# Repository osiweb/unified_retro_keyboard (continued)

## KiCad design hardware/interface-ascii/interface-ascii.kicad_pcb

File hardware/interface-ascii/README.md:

# ASCII Interface - Atmega328p

This is is a key scanner module with parallel output, and optional serial
output, supporting keyboards of up to 16 rows X 8 columns.

The ATMega 328P was selected for the sole reason that it is an architecture
familiar to many hobbyists, with an accessible programming environment and
ecosystem, in a DIP format that fits the retro look and is easy to solder for
most hobbyists. All of the ICs, other than the microcontroller, are only present
to compensate for the limited number of GPIO lines on this small 28-pin
microcontroller. Using a bigger chip would greatly simplify the hardware and
even slightly simplify the hardware layer of the firmware.

## Features
- Parallel or serial output
- Up to 8 configuration settings via an up-to-8 position DIP switch
- Apple 1, Apple 2, and SOL-20 compatible outputs. Other configurations can be
  supported by making a custom cable.
- Can decode arbitrary keyboards up 16 rows by 8 columns.
- Supports up to 3 keyboard LEDs
- Supports up to 3 "special" host outputs, such as RESET, SCREEN_CLEAR, BREAK, etc.

## Overview
- The keyboard rows are driven by a pair of 74LS138 decoders, allowing 4 GPIO
  lines to drive 16 rows.
- The columns are read in via an 8-bit shift register, controlled by 3 GPIO lines.
- One 8-bit port is used for the parallel ASCII output.
- Three GPIO lines are used to generate special outputs to the host. These could
  be RESET, BREAK, CLEAR, etc. Two of these may be configured as emulated
  open-collector drivers.
- Three GPIO lines are used to control keyboard LEDs. 

- The DIP switch is wired into row 8 (of 0-15) to reduce RAM usage and speed up
  key scanning.

- The top two parallel I/O bits can also be configured as UART I/O. This could
be used to provide serial output instead or parallel output, to support a
bootloader, or even to accept a serial input stream from another computer to
send to the host as parallel ASCII data. This last application would require
careful timing to avoid conflicts.

## Assembly Notes

The minimum functioning circuit includes 
1. the Microcontroller (U1)
1. the 74LS166 shift register (U2)
1. one 74LS138 decoder (U3). This means no DIP switch, so keymap must be
   selected at firmware build.
1. The resistor network RN1
1. The two resistors R3 and R4. If you are using the keyboard in only a parallel
configuration or only a serial configuration, then you can jumper these
resistors with a piece of wire.
1. Any connectors required.

## Optional components
### Diodes D1-D16
These diodes are intended to prevent conflicts between high and low keyboard
driver outputs. They allow the row drivers to pull rows low, but not high,
emulating open collector outputs.

If you are attaching a keyboard with no diodes, then you only need to populate
the diodes corresponding to rows on the keyboard. If the keyboard has 8 rows,
then you may want to install 8 diodes corresponding to those rows.

Note that the footprints for these diodes include a copper jumper on the TOP
copper layer. If you install any of these diodes, you should cut the jumpers for
those diodes. Otherwise the diodes do nothing.

If you are attaching a keyboard with a diode per key, then the diodes on the keys perform the same function, in addition to preventing "ghosting", so the per-row diodes do not need to be installed.

### DIP switch and associated diodes
If you don't want to select keymaps or options via the DIP switch, then you may omit the DIP switch and diodes.  If you do this, then you will have to set the keymap and all preferences in the firmware.
DIP switches, you can set all your preferences in the firmware, or just accept
the default behavior, and skip the DIP switch and Diodes D17-D20 and D24-D27.

### Second 74LS138 multiplexer (U4)
Only needed if you have more than 8 rows (including the DIP switch).

### The 74LS07 hex buffer (U5) and pullup R6
The 74LS07 is only needed if you are using LED2 or LED3 on the keyboard, or the OUT2 open
collector output.

### Diodes D21, D22, D23
Some keyboards may not wire all keys into the matrix. For example, some other
interface modules may assign special hardware functions to certain keys. Those
keys are brought directly to the keyboard connector. For the classic keyboard,
the POWER key, the '@' key, and the RUBOUT key are not directly wired. This
module wires them into the matrix via D21, D22, and D23, respectively. For
keyboards with no separately wired keys, these diodes may be omitted.

### Resistors R1, R2, R5
These resistors provide current limiting for up to three keyboard LEDs. If no
keyboard LEDs are installed, then these resistors can be ommitted.

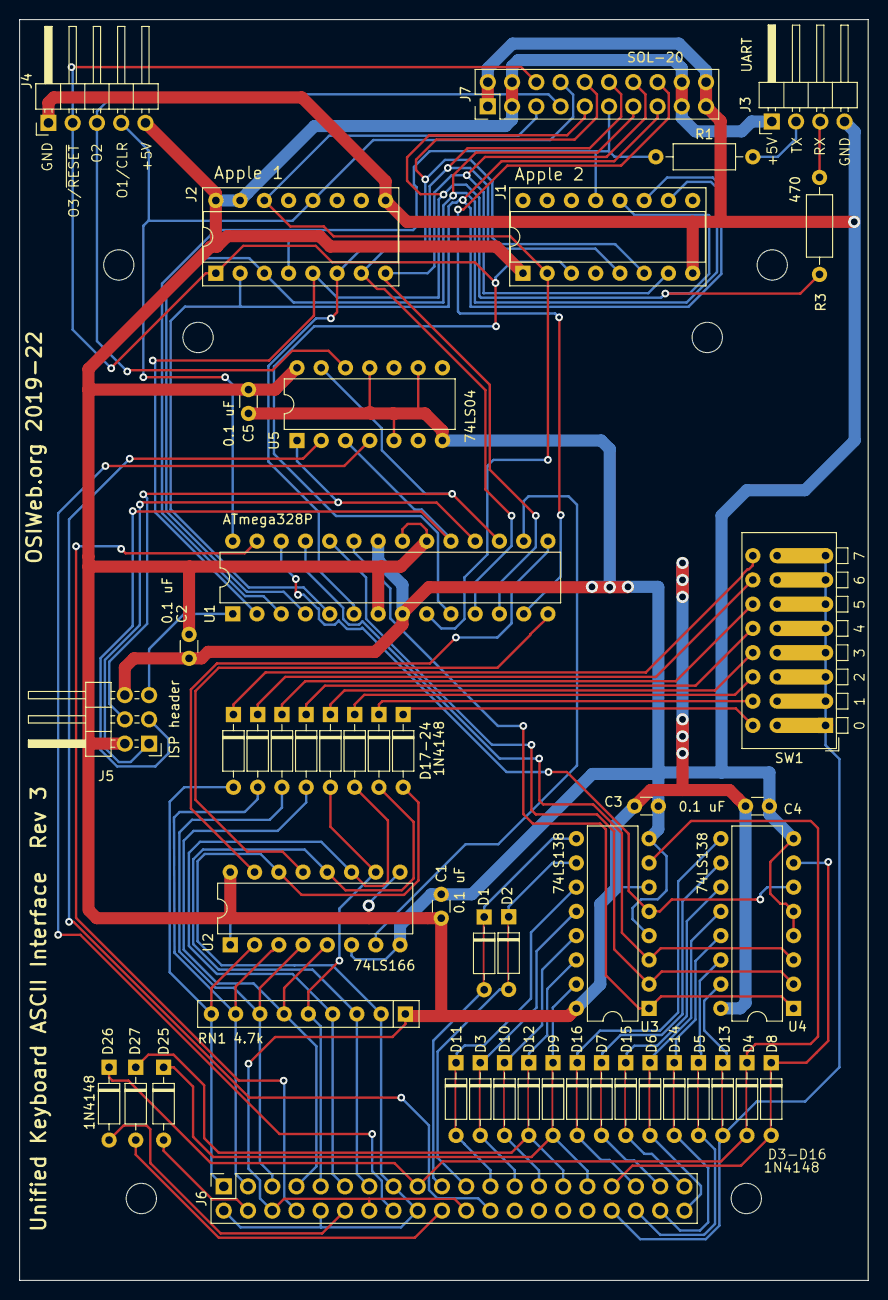
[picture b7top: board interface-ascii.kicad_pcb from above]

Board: 2 copper layers, 88.9 x 132.1 mm, 48 parts (0 on the bottom side), 81 nets.

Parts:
C1, C2, C3, C4, C5: 0.1 uF; C_Disc_D3.0mm_W1.6mm_P2.50mm
D1, D2, D3, D4, D5, D6, D7, D8, D9, D10, D11, D12, D13, D14, D15, D16: 1N4148; D_DO-35_SOD27_P7.62mm_Horizontal_bypassed
D17, D18, D19, D20, D21, D22, D23, D24, D25, D26, D27: 1N4148; D_DO-35_SOD27_P7.62mm_Horizontal
J1: Apple 2; DIP-16_W7.62mm_Socket
J2: Apple 1; DIP-16_W7.62mm_Socket
J3: UART; PinHeader_1x04_P2.54mm_Horizontal
J4: Outputs; PinHeader_1x05_P2.54mm_Horizontal
J5: ISP header; PinHeader_2x03_P2.54mm_Horizontal
J6: Keyboard; kbd_header_and_mounting_holes
J7: SOL-20; SOL20-header-vertical
R1, R3: 470; R_Axial_DIN0207_L6.3mm_D2.5mm_P10.16mm_Horizontal
RN1: 4.7k; R_Array_SIP9
SW1: Options; SW_DIP_SPSTx08_oriented_backward
U1: ATmega328P; DIP-28_W7.62mm
U2: 74LS166; DIP-16_W7.62mm
U3, U4: 74LS138; DIP-16_W7.62mm
U5: 74LS04; DIP-14_W7.62mm

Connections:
+5V: C1.1, C2.1, C3.1, C4.1, C5.1, J1.1, J2.15, J2.16, J3.1, J4.5, J5.2, J6.6, J6.14, J6.22, J7.2, J7.9, J7.12, J7.19, RN1.1 (common), U1.7 (VCC), U1.20 (AVCC), U1.21 (AREF), U2.1 (Ds), U2.9 (Clr), U2.16 (VCC), U3.6 (E3), U3.16 (VCC), U4.16 (VCC), U5.14 (VCC)
/Col0: D17.2 (A), J6.2, J6.10, J6.15, J6.18, RN1.2 (R1), U2.14 (D0)
/Col1: D21.2 (A), J6.13, RN1.3 (R2), U2.12 (D1)
/Col2: D18.2 (A), J6.11, RN1.4 (R3), U2.11 (D2)
/Col3: D22.2 (A), J6.9, RN1.5 (R4), U2.10 (D3)
/Col4: D19.2 (A), J6.7, RN1.6 (R5), U2.5 (D4)
/Col5: D23.2 (A), J6.5, RN1.7 (R6), U2.4 (D5)
/Col6: D20.2 (A), J6.3, RN1.8 (R7), U2.3 (D6)
/Col7: D24.2 (A), J6.1, RN1.9 (R8), U2.2 (D7)
/D0: J1.12, J2.5, J7.5, R3.1, U1.2 (PD0)
/D1: J1.13, J2.4, J7.6, R1.1, U1.3 (PD1)
/D2: J1.10, J2.3, J7.7, U1.4 (PD2)
/D3: J1.11, J2.2, J7.8, U1.5 (PD3)
/D4: J1.6, J2.6, J7.15, U1.6 (PD4)
/D5: J1.5, J2.7, J7.16, U1.11 (PD5)
/D6: J1.7, J2.8, J7.17, U1.12 (PD6)
/D7: J7.18, U1.13 (PD7)
/LED1: J6.8, U1.27 (PC4)
/MISO-LED3: J5.1, U1.18 (MISO/PB4), U5.1
/MOSI-OUT2: J5.4, U1.17 (MOSI), U5.13
/OUT1: J2.12, J4.4, J7.14, U1.28 (PC5)
/OUT2: J4.3, J7.4, U5.12
/OUT3: J1.3, J2.1, J4.2, J7.13, U1.10 (PB7)
/Row0: D9.2 (A), D25.1 (K), J6.31
/Row1: D12.2 (A), D27.1 (K), J6.29
/Row2: D10.2 (A), J6.27
/Row3: D3.2 (A), J6.25
/Row4: D11.2 (A), J6.23
/Row5: D2.2 (A), J6.21
/Row6: D1.2 (A), J6.19
/Row7: D4.2 (A), D26.1 (K), J6.17
/Row8: D13.2 (A), J6.34, SW1.1, SW1.2, SW1.3, SW1.4, SW1.5, SW1.6, SW1.7, SW1.8
/Row9: D5.2 (A), J6.36
/Row10: D14.2 (A), J6.38
/Row11: D6.2 (A), J6.40
/Row12: D15.2 (A), J6.39
/Row13: D7.2 (A), J6.37
/Row14: D16.2 (A), J6.35
/Row15: D8.2 (A), J6.33
/Rx: J3.3, R3.2
/SCK-LED2: J5.3, U1.19 (SCK/PB5), U5.3
/Tx: J3.2, R1.2
/~RESET: J5.5, U1.1 (~RESET)
/~STROBE: J1.2, J2.14, J7.3, U1.9 (PB6)
GND: C1.2, C2.2, C3.2, C4.2, C5.2, J1.8, J2.9, J3.4, J4.1, J5.6, J7.1, J7.10, J7.11, J7.20, U1.8 (GND), U1.22 (GND), U2.6 (CK_INH), U2.8 (GND), U3.4 (E1), U3.8 (GND), U4.4 (E1), U4.5 (E2), U4.8 (GND), U5.5, U5.7 (GND), U5.9, U5.11
unnamed: D1.1 (K), U3.9 (O6)
unnamed: D2.1 (K), U3.10 (O5)
unnamed: D3.1 (K), U3.12 (O3)
unnamed: D4.1 (K), U3.7 (O7)
unnamed: D5.1 (K), U4.14 (O1)
unnamed: D6.1 (K), U4.12 (O3)
unnamed: D7.1 (K), U4.10 (O5)
unnamed: D8.1 (K), U4.7 (O7)
unnamed: D9.1 (K), U3.15 (O0)
unnamed: D10.1 (K), U3.13 (O2)
unnamed: D11.1 (K), U3.11 (O4)
unnamed: D12.1 (K), U3.14 (O1)
unnamed: D13.1 (K), U4.15 (O0)
unnamed: D14.1 (K), U4.13 (O2)
unnamed: D15.1 (K), U4.11 (O4)
unnamed: D16.1 (K), U4.9 (O6)
unnamed: D17.1 (K), SW1.16
unnamed: D18.1 (K), SW1.14
unnamed: D19.1 (K), SW1.12
unnamed: D20.1 (K), SW1.10
unnamed: D21.1 (K), SW1.15
unnamed: D22.1 (K), SW1.13
unnamed: D23.1 (K), SW1.11
unnamed: D24.1 (K), SW1.9
unnamed: D25.2 (A), J6.4
unnamed: D26.2 (A), J6.12
unnamed: D27.2 (A), J6.20
unnamed: J6.16, U5.4
unnamed: J6.24, U5.2
unnamed: U1.14 (PB0), U2.13 (Qh)
unnamed: U1.15 (PB1), U2.15 (SH_~LD)
unnamed: U1.16 (PB2), U2.7 (CLK)
unnamed: U1.23 (PC0), U3.1 (A0), U4.1 (A0)
unnamed: U1.24 (PC1), U3.2 (A1), U4.2 (A1)
unnamed: U1.25 (PC2), U3.3 (A2), U4.3 (A2)
unnamed: U1.26 (PC3), U3.5 (E2), U4.6 (E3)

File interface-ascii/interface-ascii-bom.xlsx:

Bill of Materials, ASCII Interface, Rev 2.8
Referece Designator | Qty | Label | Fitted | Manufacturer | Manufacturer PN | Substitution OK | Value | Datasheet | Comments
C1-C5 | 5 | 0.1 uF | Y | Murata | RCER71E104K0A2H3B | Y | 0.1 uF | ~
D1-D16 | 16 | 1N4148 | N | Vishay | 1N4148 | Y | Gen. Purpose/switching | https://assets.nexperia.com/documents/data-sheet/1N4148_1N4448.pdf | Install only for matrix without diodes. Cut jumper if installed
D17-D27 | 11 | 1N4148 | Y | Vishay | 1N4148 | Y | Gen. Purpose/switching | https://assets.nexperia.com/documents/data-sheet/1N4148_1N4448.pdf
J1 | 1 | Apple 2 | Y | 3M | 4816-3000-CP | Y | 16-pin Dual-wipe DIP socket | ~ | Install for Apple 2. Dual Wipe recommended to reduce insertion force
J2 | 1 | Apple 1 | Y | 3M | 4816-3000-CP | Y | 16-pin Dual-wipe DIP socket | ~ | Install for Apple 2. Dual Wipe recommended to reduce insertion force
J3 | 1 | UART | Y | Molex | 22-28-8040 | Y | 1x4 0.1" right angle header | ~ | Install for UART
J4 | 1 | Outputs | Y | Molex | 22-28-8050 | Y | 1x5 0.1" right angle header | ~ | ~
J5 | 1 | ISP header | Y | Molex | 90122-0763 | Y | 2x3 0.1" right angle header | ~ | ~
J6 | 1 | Keyboard | Y | Molex | 90131-0140 | Y | 2x20 0.1" vertical header | ~ | ~
J7 | 1 | SOL-20 | Y | Molex | 90122-0770 | Y | 2x10 0.1" right angle header | ~ | Install for SOL-20
R3, R4 | 2 | 470 | Y | Yageo | MFR-25FTE52-470R | Y | 470 | ~ | ~
RN1 | 1 | 4.7k | Y | Bourns | 4609X-101-472LF | Y | 4.7k |  | ~
SW1 | 1 | Options | Y | CTS | 195-8MST | Y | 8-pos DIP switch | ~ | ~
U1 | 1 | ATmega328P | Y | Atmel (Microchip) | ATMEGA328P-PU | N | ATmega328P | http://ww1.microchip.com/downloads/en/DeviceDoc/ATmega48A-PA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 | ~
U2 | 1 | 74LS166 | Y | Texas Instruments | SN74LS166AN | Y | 74LS166 | https://www.ti.com/lit/ds/symlink/sn74ls166a | ~
U3, U4 | 2 | 74LS138 | Y | Texas Instruments | SN74LS138N | Y | 74LS138 | http://www.ti.com/lit/gpn/sn74LS138 | ~
U5 | 1 | 74LS04 | Y | Texas Instruments | SN74LS04N | Y | 74LS04 | www.ti.com/lit/ds/symlink/sn74ls04.pdf | ~

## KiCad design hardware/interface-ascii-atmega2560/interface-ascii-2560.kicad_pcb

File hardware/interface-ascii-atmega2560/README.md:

# ASCII Interface - Atmega2560

This is is a key scanner module with parallel output, and optional serial
output, supporting keyboards of up to 16 rows X 8 columns.  This design uses the ATMega2560, since it's an easy port from the ATMega328P, which was initially selected for the sole reason of being familiar to hobbyists. The 2560 has much more I/O, which simplifies the design, assembly, and firmware, and opens up some additional possibilities. 

## Features
- Parallel or serial output
- Up to 8 configuration settings via an up-to-8 position DIP switch
- Apple 1, Apple 2, and SOL-20 compatible outputs. Other configurations can be
  supported by making a custom cable.
- Can decode arbitrary keyboards up 16 rows by 8 columns.
- Supports up to 3 keyboard LEDs
- Supports up to 3 "special" host outputs, such as RESET, SCREEN_CLEAR, BREAK, etc.
- Socket for custom connector

## Differences from ATMega328P version
- Backward compatible with the ATMega328P version, with following enhancements:
1. All the TTL outputs can be regualar push-pull TTL, open-collector, or open-emitter. In the
   328P version, changing between regular TTL output and open-collector on
   Output 2 required changing an IC.
1. The serial port no longer shares lines with the parallel output port, so both
   serial I/O and parallel output can be used at the same time without risk of
   conflict. However, serial I/O is not yet supported in the firmware.
1. Because the rows are no longer driven by a 4-to-16 decoder circuit, and the
   columns are no longer read via a shift register, the row and column lines can
   be used for both input and output, which allows this board to interface with
   OSI keyboards directly (not yet supported in firmware).
   
## Overview
- Two GPIO ports are used to drive the row outputs, and one GPIO port is used to
  read the columns.
- One 8-bit port is used for the parallel ASCII output.
- Three GPIO lines are used to generate special outputs to the host. These could
  be RESET, BREAK, CLEAR, etc. These may be configured as open-collector (Hi-Z
  for HI, GND for LO), or open-emitter (5V for high, Hi-Z for LO).
- Three GPIO lines are used to control keyboard LED, or other keyboard functions.
- A serial (UART) port is provided. This could be used to provide serial output
instead or parallel output, to support a bootloader, or even to accept a serial
input stream from another source to send to the host as parallel ASCII data.
- JTAG port is provided for programming and debugging
- Two custom connectors (16-pin DIP and 1x25 0.1" header) are provided to allow
  custom ASCII interfaces, or custom keyboard matrix interface.
  
## Assembly Notes

1. Solder the surface-mount microcontroller first. Be sure to match pin 1 to the
   dot on the silk-screen layer.
1. Next, install the surface mount crysta, Y1.  The orientation is not important.
1. Next, solder in the Diodes D1-D3 and D4-D11
1. Do not populate diodes D12-D27. These diodes are jumpered short. If you are
   using a key matrix with no diodes, then cut the jumpers with an x-acto knife
   and populate the diodes.
1. Install all the capacitors. These are all 0.1 uF ceramic capacitors with 0.1"
   lead spacing. Many capacitors with 0.2" lead spacing are actually 0.1"
   emerging from the body, bent to 0.2", and can be straightened back to 0.1".
1. Next, solder in the resitor R1 and Resistor network RN1.
1. Install DIP switch SW1.
1. Install connector J7 
1. Install the In-circuit Serial Programming (ISP) header, J6. (right-angle, 2x3
   0.100")
1. (Optional) If you will be the digital outputs, or if you will be attaching
   switches or other sources of open-collector signals (such as RESET), then
   install connector J4 (right-angle, 1x5 0.100")
1. (Optional) If you will be using the serial port, install the serial header
   J3. (right angle, 1x4 0.100")
1. If you will be using the Apple 1 connector, install the DIP socket J1 (16-pin
   dip). If you plan to insert and remove the cable many times, a dual-wipe
   socket may be preferable to machine-pin, since it has a lower insertion
   force, and you will be less likely to bend pins. If you plan to insert the
   cable once and leave it forever, I suggest a machine-pin DIP socket.
1. If you will be using the Apple 2 connector, install the DIP socket J2 (16-pin
   dip).  The note for the Apple 1 connector selection applies here as well.
1. If you will be using the SOL-20 connector, install connector J5 (vertical
   2x10 0.100")

configuration or only a serial configuration, then you can jumper these
resistors with a piece of wire.
1. Any connectors required.

## Optional components
### Diodes D1-D16
These diodes are intended to prevent conflicts between high and low keyboard
driver outputs. They allow the row drivers to pull rows low, but not high,
emulating open collector outputs.

If you are attaching a keyboard with no diodes, then you only need to populate
the diodes corresponding to rows on the keyboard. If the keyboard has 8 rows,
then you may want to install 8 diodes corresponding to those rows.

Note that the footprints for these diodes include a copper jumper on the TOP
copper layer. If you install any of these diodes, you should cut the jumpers for
those diodes. Otherwise the diodes do nothing.

If you are attaching a keyboard with a diode per key, then the diodes on the keys perform the same function, in addition to preventing "ghosting", so the per-row diodes do not need to be installed.

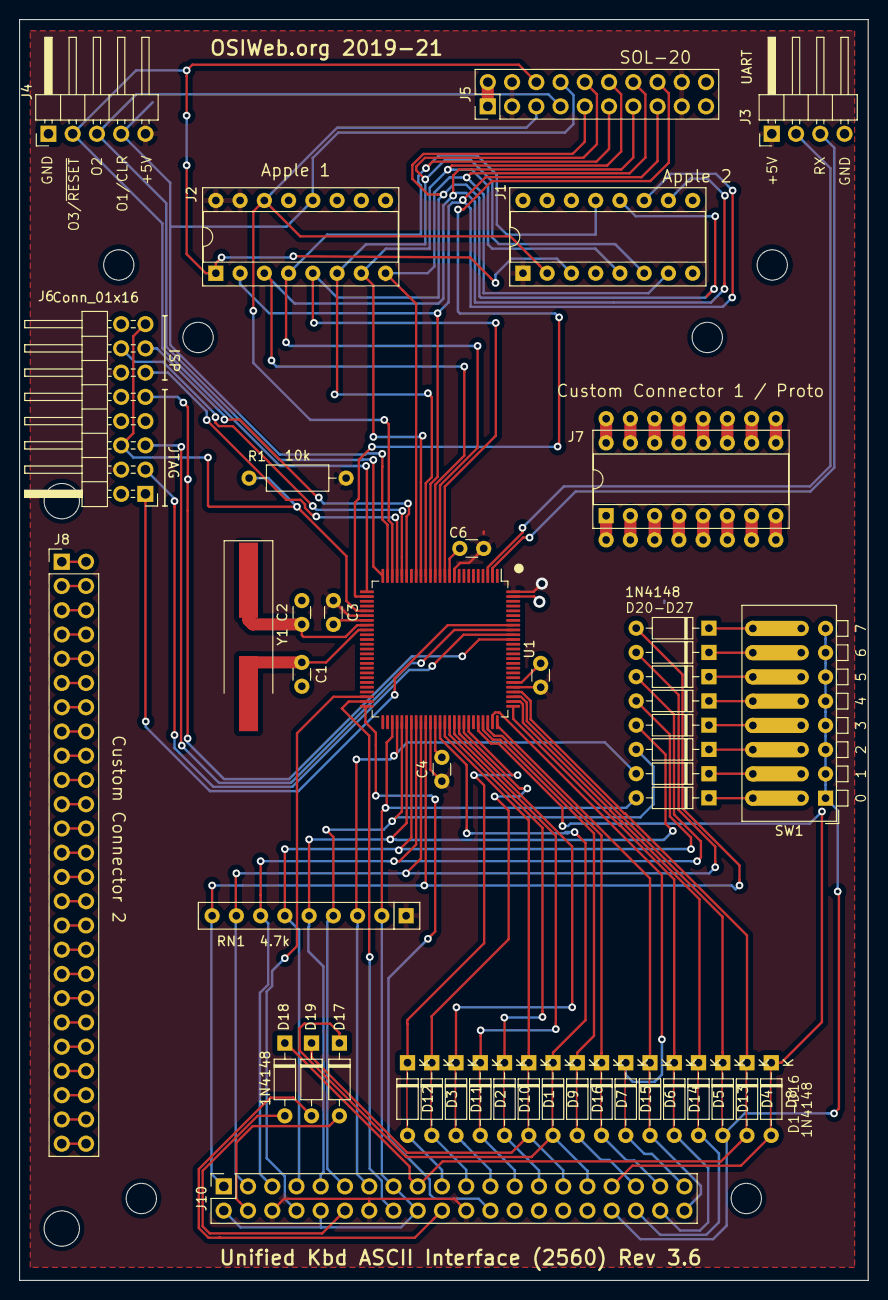
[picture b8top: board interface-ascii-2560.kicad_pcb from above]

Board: 2 copper layers, 88.9 x 132.1 mm, 49 parts (0 on the bottom side), 80 nets.

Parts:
C1, C2: 36pf; C_Disc_D3.0mm_W1.6mm_P2.50mm
C3, C4, C5, C6: 0.1 uF; C_Disc_D3.0mm_W1.6mm_P2.50mm
D1, D2, D3, D4, D5, D6, D7, D8, D9, D10, D11, D12, D13, D14, D15, D16: 1N4148; D_DO-35_SOD27_P7.62mm_Horizontal_bypassed
D17, D18, D19, D20, D21, D22, D23, D24, D25, D26, D27: 1N4148; D_DO-35_SOD27_P7.62mm_Horizontal
J1: Apple 2; DIP-16_W7.62mm_Socket
J2: Apple 1; DIP-16_W7.62mm_Socket
J3: UART; PinHeader_1x04_P2.54mm_Horizontal
J4: Conn_01x05; PinHeader_1x05_P2.54mm_Horizontal
J5: SOL-20; SOL20-header-vertical
J6: Conn_01x16; PinHeader_2x08_P2.54mm_Horizontal
J7: Custom Connector 1 / Proto; DIP-16_W7.62mm_Proto
J8: Custom Connector 2; ExpansionHeader_1x25_P2.54
J10: Keyboard; kbd_header_and_mounting_holes
MH1, MH2: Apple II; MountingHole_3.7mm
R1: 10k; R_Axial_DIN0207_L6.3mm_D2.5mm_P10.16mm_Horizontal
RN1: 4.7k; R_Array_SIP9
SW1: Options; SW_DIP_SPSTx08_Piano_CTS_Series194-8MSTN_W7.62mm_P2.54mm
U1: ATmega2560-16AU; TQFP-100_14x14mm_P0.5mm
Y1: 16.000 MHz; Crystal_SMD_HC49-SD_HandSoldering

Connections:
/Col0: D20.2, J10.2, J10.10, J10.15, J10.18, RN1.2, U1.53
/Col1: D24.2, J10.13, RN1.3, U1.54
/Col2: D21.2, J10.11, RN1.4, U1.55
/Col3: D25.2, J10.9, RN1.5, U1.56
/Col4: D22.2, J10.7, RN1.6, U1.57
/Col5: D26.2, J10.5, RN1.7, U1.58
/Col6: D23.2, J10.3, RN1.8, U1.59
/Col7: D27.2, J10.1, RN1.9, U1.60
/D0: J1.12, J2.5, J5.5, U1.12
/D1: J1.13, J2.4, J5.6, U1.13
/D2: J1.10, J2.3, J5.7, U1.14
/D3: J1.11, J2.2, J5.8, U1.15
/D4: J1.6, J2.6, J5.15, U1.16
/D5: J1.5, J2.7, J5.16, U1.17
/D6: J1.7, J2.8, J5.17, U1.18
/D7: J5.18, U1.27
/LED1: J10.8, U1.48
/LED2: J10.16, U1.49
/LED3: J10.24, U1.50
/MISO: J6.11, U1.22
/MOSI: J6.14, U1.21
/OUT1: J2.12, J4.4, J5.14, U1.24
/OUT2: J4.3, J5.4, U1.25
/OUT3: J1.3, J2.1, J4.2, J5.13, U1.26
/Row0: D9.2, D17.1, J10.31
/Row1: D1.2, D19.1, J10.29
/Row2: D10.2, J10.27
/Row3: D2.2, J10.25
/Row4: D11.2, J10.23
/Row5: D3.2, J10.21
/Row6: D12.2, J10.19
/Row7: D4.2, D18.1, J10.17
/Row8: D13.2, J10.34, SW1.1, SW1.2, SW1.3, SW1.4, SW1.5, SW1.6, SW1.7, SW1.8
/Row9: D5.2, J10.36
/Row10: D14.2, J10.38
/Row11: D6.2, J10.40
/Row12: D15.2, J10.39
/Row13: D7.2, J10.37
/Row14: D16.2, J10.35
/Row15: D8.2, J10.33
/Rx: J3.3, U1.2
/SCK: J6.13, U1.20
/TCK: J6.1, U1.93
/TDI: J6.9, U1.90
/TDO: J6.3, U1.91
/TMS: J6.5, U1.92
/Tx: J3.2, U1.3
/~RESET: J6.6, J6.15, R1.2, U1.30
/~STROBE: J1.2, J2.14, J5.3, U1.23
GND: C1.2, C2.2, C3.2, C4.2, C5.2, C6.2, J1.8, J2.9, J3.4, J4.1, J5.1, J5.10, J5.11, J5.20, J6.2, J6.10, J6.16, U1.11, U1.32, U1.62, U1.81, U1.99
unnamed: C1.1, U1.34, Y1.2
unnamed: C2.1, U1.33, Y1.1
unnamed: D1.1, U1.64
unnamed: D2.1, U1.66
unnamed: D3.1, U1.68
unnamed: D4.1, U1.79
unnamed: D5.1, U1.77
unnamed: D6.1, U1.75
unnamed: D7.1, U1.73
unnamed: D8.1, U1.71
unnamed: D9.1, U1.63
unnamed: D10.1, U1.65
unnamed: D11.1, U1.67
unnamed: D12.1, U1.69
unnamed: D13.1, U1.78
unnamed: D14.1, U1.76
unnamed: D15.1, U1.74
unnamed: D16.1, U1.72
unnamed: D17.2, J10.4
unnamed: D18.2, J10.12
unnamed: D19.2, J10.20
unnamed: D20.1, SW1.16
unnamed: D21.1, SW1.14
unnamed: D22.1, SW1.12
unnamed: D23.1, SW1.10
unnamed: D24.1, SW1.15
unnamed: D25.1, SW1.13
unnamed: D26.1, SW1.11
unnamed: D27.1, SW1.9
VCC: C3.1, C4.1, C5.1, C6.1, J1.1, J2.15, J2.16, J3.1, J4.5, J5.2, J5.9, J5.12, J5.19, J6.4, J6.12, J10.6, J10.14, J10.22, R1.1, RN1.1, U1.10, U1.31, U1.61, U1.80, U1.100

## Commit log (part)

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2020-04-21 Add OSI interface schematic
    Provides a keyboard interface to interface with OSI computers. Equivalent to an
    OSI 542C.
    - Includes sound circuits
    - Includes RESET delay circuit
    - SHIFT LOCK can be mechanical push-on/push-off or soft toggle, selectable by
    jumper.
2020-04-27 Initial cut of OSI 542 keyboard scan support
2020-04-27 Fix unconnected wire to decoder for rows 8-15
2020-05-05 Minor cleanups
2020-05-06 Enable output hook in main()
2020-05-12 Moved clock speed definition (F_CPU) to arch header file
2020-05-12 Updae 3D image
2020-05-13 More gitignore updates
2020-05-14 Cleanups on ASCII interface PCBs, 328P and 2560 versions
    - Clean up diode positioning and numbering
    - Remove 3D models for devices that are not normally fitted
    - clean up labeling
    - update README files to match PCBs.
2020-05-14 Add additional mounting holes to ASCII interface PCBS and Sol-20 PCB
2020-05-19 minor hook cleanups
    - Rename asdf_hook_do() to asdf_hook_execute()
    - asdf.c: Call asdf_hook_execute() for ASDF_HOOK_EACH_SCAN hook call in the scan
    routine, instead of getting then calling the function via hook_get()
    - asdf.c: move the fetch of scan function hook outside the scan loop.
2020-05-21 addon board uses 74HC14
2020-05-27 Add image to README
2020-06-02 Add mounting holes for Apple II keyboard
2020-06-03 Various PCB cleanup
    - Fix position of holes around 1x25 connector to match Apple 2 keyboard
    - silk screen fixes
    - minor trace shoves.
2020-06-05 Change photo width
2020-06-06 Update README to add OSI module
2020-06-16 Update gitignore
2020-06-17 Tiny adjustment to stabilizer post width gauge
2020-06-23 Added combined SMT-Thru-hole Diode for keyboard
2020-06-25 Restore cherry MX center hole to 0.157" and pull back soldermask from hole
2020-06-29 Replaced standard 20-pin header with header+mounting holes
2020-07-08 Start a build guide
2020-07-09 More Build notes cleanups.
2020-07-09 Removed extraenous image tag
2020-07-13 More build details and pictures.
2020-07-17 Apply 328P readme update to main branch.
2020-08-06 Notation fixes for pointers to functions
2020-08-06 Update components in SMT encoder board to include LCSC part numbers
2020-08-17 Update footprints to add soldermask clearance around Cherry MX posts
2020-08-22 Removed old keyboard cutout templates for classic keyboard.
    cutouts are now included in the classic keyboard PCB file on separate layers.
2020-12-29 Modify to use DIP switch or jumpers
    - Add combined DIP-switch/Jumper footprint to footprint library
    - Fix Apple2-encoder and interface-ascii-atmega2560 schematics and PCB to use
    new footprint.
2021-01-01 Update README for integrated sol keyboard pcb
    Add images including rendering of integrated PCB
2021-01-24 pcb file consistency update
2021-02-13 Updated README.md with image of PCB
2021-03-05 Rebase newmaps branch to master
    (WARNING: WIP) Gathered Work-in-progress on alternate keymap defs
    Exploratory branch. Code is messy and untested.
    Examining creating a module for each keymap rather than header file.
2021-03-05 Remove redundant NUM_ROWS and NUM_COLS definition from test keymap
2021-03-08 newmaps passes all tests with cmake build.
2021-05-19 Add multiple kicad footprints
    - mounting posts (for futaba)
    - aligner tool
    - bending guide
2021-08-08 Added silk screen annotations for connectors.
2021-09-21 Fix subscript on Sol map
    - Change from 4 to 2, since only 3 maps for now.
2021-11-09 BUGFIX: 328P OUT2 output was changing OUT1
    This appears to have been a cut-paste typo in the asdf_arch_out2_set() function
    in asdf_arch_atmega328p.c. The port was set to OUT2, but the bit was OUT1.
2021-11-28 Initialze buffers before other subsystems
    Other subsystems may want to use buffers for output, e.g., for status
    and debug.
2021-11-28 Fix library-related indirection bug
    Accessing library functions via function pointer seems to cause a reset.
    Still investigating the cause.
    - compile keymaps subdir as part of main src cmakefile, rather than as a
    separate library.
    - rather than setup table of function pointers and using an indirection
    in the main code, set up a jump table (switch). This is cleaner.
2021-11-29 Typo fixes to classic keycap spreadsheet
2021-12-04 Fix slow repeat on some columns (Fixes #15)
    Removed a bit of logic from the column bit test code that created
    different scan rates for different columns.
2021-12-05 Apple2 u/l keyboard has CAPS by default.
    Start LED off, and turn on by activating CAPS
2021-12-11 Remove extraneous chars.
2021-12-21 Keycaps for SAIL keyboard
2022-03-01 Add missing keymap header files
2022-09-01 Fix typo in src/CMakeLists.txt
    for function create_keymap_valid, return statement had wrong function name.
2022-09-08 Add dash before trigger branch names
2022-09-08 Fixes to README
2022-12-03 Update eeprom-spec document
2022-12-30 Deploying to gh-pages from @ osiweb/unified_retro_keyboard@ca8cff670a6721483ef4bf035a91c3244b3f608b 🚀
2022-12-30 Add user-bindable function to print ascii chars
2023-01-02 Deploying to gh-pages from @ osiweb/unified_retro_keyboard@f4ace5a9cb2e62c3fa50d06815eb32e638de5880 🚀
2023-01-02 Deploying to gh-pages from @ osiweb/unified_retro_keyboard@6a3c0073e599fa61d0ce5376e8a73e8a775972f1 🚀
2023-03-17 Initial commit.
2023-03-18 Add Franklin ACE 1000 keyboard.
2023-04-18 Define default row scanner in arch headers
    - in header files, change ASDF_ARCH_DEFAULT_SCANNER to
    ASDF_ARCH_DEFAULT_ROW_SCANNER
    - remove unused ASDF_NUM_KEYMAPS definition in asdf_keymap_setup.h.in
2023-04-22 Add mounting holes to OSI keyboard cutout
    - update OSI mounting hole footprint to include holes on eco2 so they
    will be included with DXF exports of the OSI keyboard cutout on Eco2
2023-05-08 Add franklin ace PCB
2023-08-04 Moved some keys to better position
2023-11-22 OSI Interface: Add special keys to repo.
2023-12-05 Add some mounting hardware
2025-11-22 symbol updates
2025-11-26 add asdf2 plan
2026-02-08 Revert to commit 5510652
    Dispatch changes should have only been commited to a development branch.
    Here we revert to the original switch statement dispatchers
2026-05-26 add minimal simavr runner that loads an avr ELF and exits
    - accepts --target / --keymap / --elf plus --verbose, --vcd, --gdb
    stubs that are wired in by later tasks.
    - links libsimavr only (libelf is pulled transitively; libelf-dev is
    not installed on Ubuntu 24.04, so -lelf is dropped from the link line).
    - uses memset to zero elf_firmware_t instead of brace-init to avoid
    -Wmissing-field-initializers from the simavr struct layout.
2026-05-26 harden capture module: null-check cap_pop, dedup cap_init, expand test
    - cap_pop now asserts out != NULL so misuse is caught at the call
    site (the strobe-edge notifier in task 6 will call it in a loop).
    - cap_init defined in terms of cap_clear so the two cannot drift apart.
    - test_capture no longer puts cap_pop calls inside assert() expressions
    (would silently no-op under NDEBUG); covers fill-to-capacity exactly
    and verifies the wrap-around tail by popping two records after the
2026-05-26 record optional VCD trace of watched pins
    - --vcd PATH triggers libsimavr avr_vcd_init/start/stop with the data
    port, strobe, LEDs, and lo row port wired as signals.
    - on test failure in CI, this trace is uploaded as an artifact for
    offline inspection in gtkwave.
2026-05-26 add per-keymap simavr test headers for 5 additional keymaps
    - add asdf_simavr_test_classic_caps.h (DIP=1)
    - add asdf_simavr_test_apple2.h (DIP=2)
    - add asdf_simavr_test_apple2_caps.h (DIP=3)
    - add asdf_simavr_test_sol.h (DIP=4)
    - add asdf_simavr_test_ace1000.h (DIP=5)
    - wire all five into pick_keymap() in asdf_simavr_runner.c
2026-05-26 update README: family A now runs full event-driven tests
    - drop the boot-only section; the harness now emulates the serial
    shift-register column read on family A (atmega328p/168p), so all
    four supported targets run the same event sequence.
    - keep --boot-only documented as a runner flag for future use when
    bringing up new targets before their column wiring is in place.
    - step 5 of the add-a-keymap recipe simplifies now that there's only
2026-05-27 ci: install libelf-dev for integration_test
    030cada added an explicit `find_library(ELF_LIBRARY)` with FATAL_ERROR,
    so libelf is now a build-time requirement on Debian, not just a
    transitive runtime dep of libsimavr.
2026-05-28 Deploying to gh-pages from @ osiweb/unified_retro_keyboard@1773958cbafa9a9cbe5e492174f710c770b4f6e9 🚀
2026-05-28 add --mode flag and dispatch scaffolding to simavr runner
    - new --mode events|identity|string flag, default 'events'
    - 'events' branch preserves existing behavior verbatim
    - 'identity' and 'string' branches error cleanly with a not-yet-
    implemented message; subsequent commits will land each mode
2026-05-28 redesign identity test to trigger ID via user-function key
    - empirical finding: the firmware does not print an identity string
    at boot. Each keymap binds its ID hook (e.g., ASDF_HOOK_USER_10
    for classic, fired by ACTION_FN_10) to a user-function action in
    the keymap matrix; the print train fires only when the user
    presses the corresponding key combination.
    - sim_identity_test_t extended with trigger_key, trigger_modifier,
2026-05-28 implement string mode dispatch in simavr runner
    - pick_string_test() stub returns NULL; per-keymap data populates
    it in subsequent commits
    - string_mod_coord() picks the right modifier coord for SHIFT,
    CAPS, or CTRL from the test struct (mirrors identity_mod_coord
    helper)
    - main()'s string branch walks the step array: KEY presses do a
